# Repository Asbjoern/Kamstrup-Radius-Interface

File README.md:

# Kamstrup-Radius Interface
 ESP8266 interface for Kamstrup (Radius provided) electricity meter

Please also have a look the ESPHome component based on this code and working on the HAN module:\
https://github.com/Asbjoern/ESPHome-Kamstrup-Radius

This project interfaces with the Kampstrup electricity meter provided by Radius in Denmark.\
It decrypts the messages pushed on the HAN port and publishes the readings on MQTT.

There is also a proof of concept Python3 script (Kamstrup reader.py). Reads serialport connected to meter, decrypts, parses and publishes result to mqtt.  
Based on Python example provided by Radius.

## Project contains:
* HAN module for the Radius provided Kamstrup Omnipower electricity meters
* Arduino based software for a ESP8266 module. For receiving, decrypting and parsing push messages from meter.
* Publish data to MQTT

## Project uses: 
* Relevant files from mbed TLS library https://tls.mbed.org/
* Modified mbusparser library from Jalla2000's norwegian project https://github.com/jalla2000/kamstrup-mqtt
* Use Wifimanager library (or similar) to get captive portal and configuration

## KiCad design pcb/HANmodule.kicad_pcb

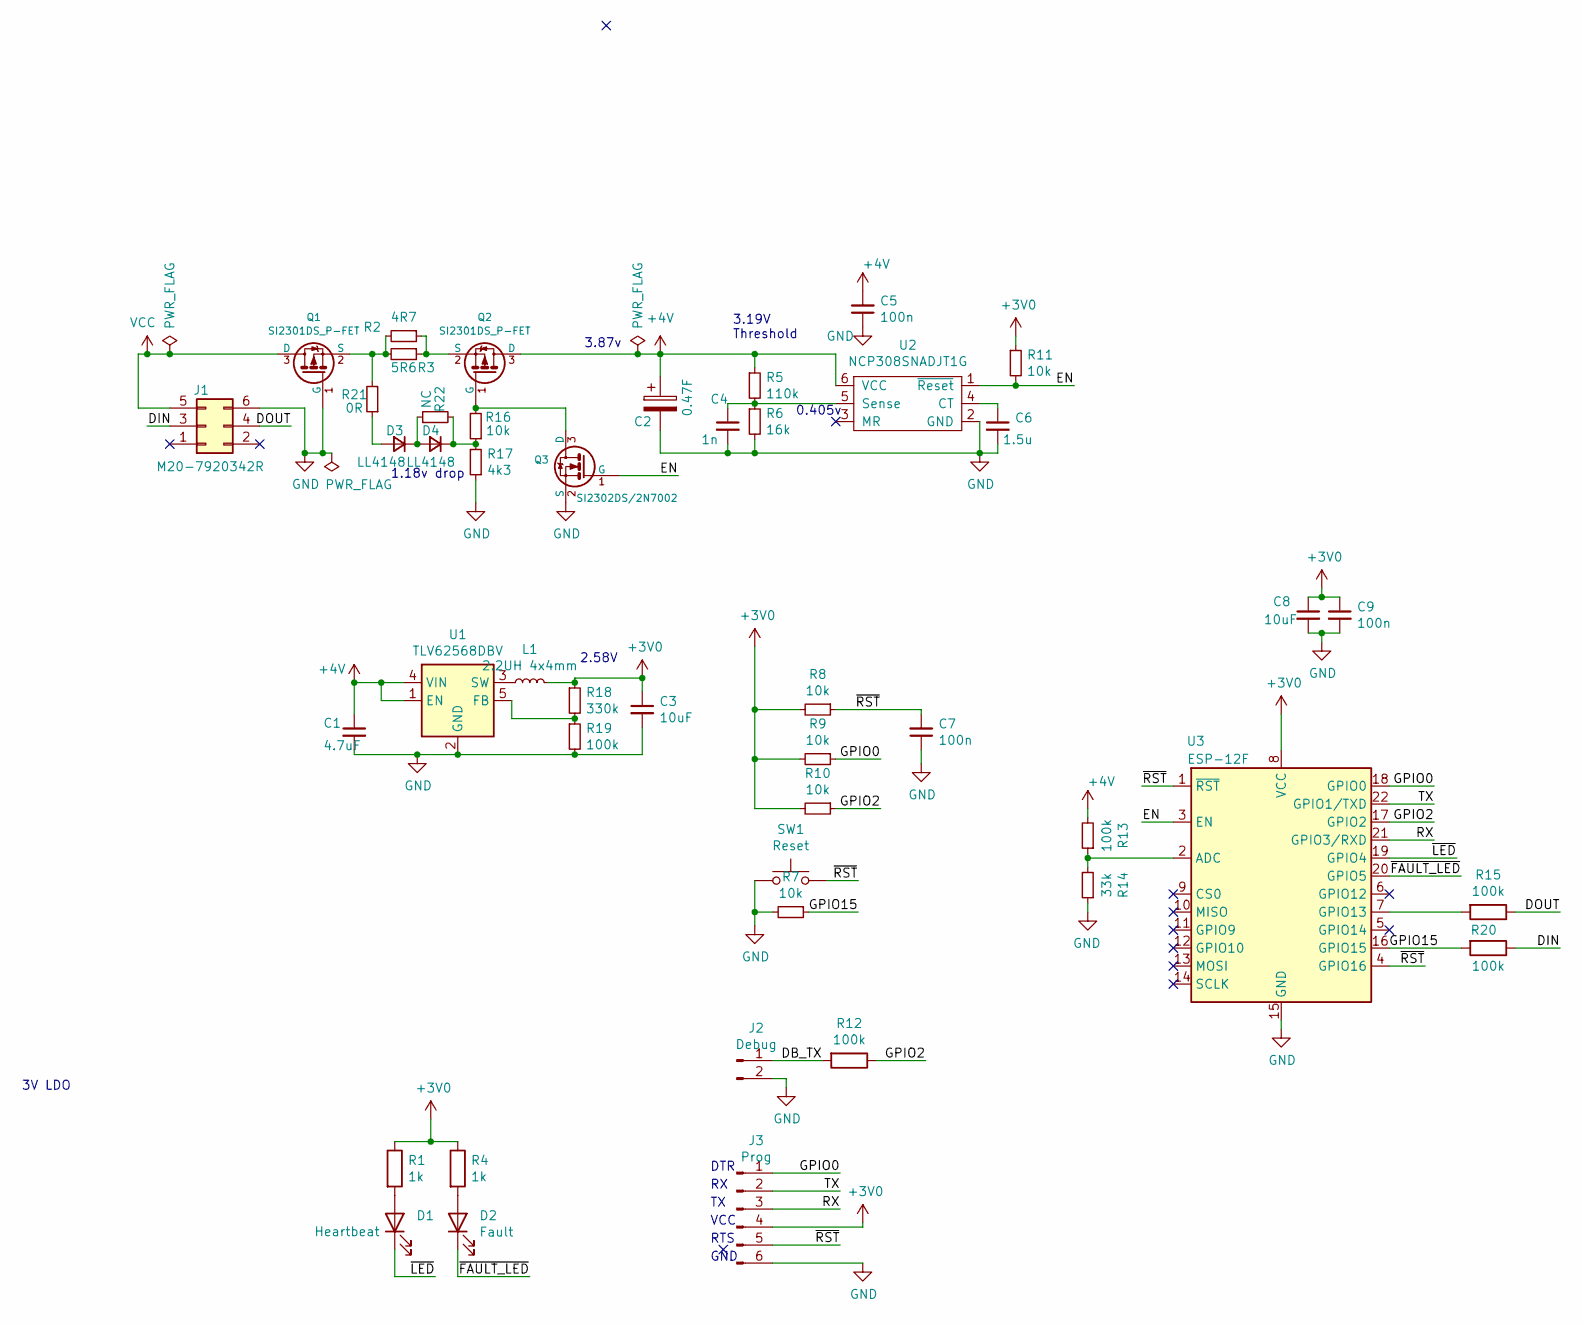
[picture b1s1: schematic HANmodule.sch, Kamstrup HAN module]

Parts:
C1: 4.7uF; C_0603_1608Metric
C2: 0.47F; c_sup 17,3x15x8.5P12
C3, C8: 10uF; C_0603_1608Metric_Pad1.05x0.95mm_HandSolder
C4: 1n; C_0603_1608Metric_Pad1.05x0.95mm_HandSolder
C5, C7, C9: 100n; C_0603_1608Metric_Pad1.05x0.95mm_HandSolder
C6: 1.5u; C_0603_1608Metric_Pad1.05x0.95mm_HandSolder
D1: Heartbeat; LED_0603_1608Metric
D2: Fault; LED_0603_1608Metric
D3, D4: LL4148; D_MiniMELF
J1: M20-7920342R
J2: Debug; PinHeader_1x02_P2.54mm_Horizontal
J3: Prog; PinHeader_1x06_P2.54mm_Horizontal
L1: 2.2UH 4x4mm; L_Bourns-SRN4018
Q1, Q2: SI2301DS_P-FET; SOT-23
Q3: SI2302DS/2N7002; SOT-23
R1, R4: 1k; R_0603_1608Metric_Pad1.05x0.95mm_HandSolder
R2: 4R7; R_0603_1608Metric_Pad1.05x0.95mm_HandSolder
R3: 5R6; R_0603_1608Metric_Pad1.05x0.95mm_HandSolder
R5: 110k; R_0603_1608Metric_Pad1.05x0.95mm_HandSolder
R6: 16k; R_0603_1608Metric_Pad1.05x0.95mm_HandSolder
R7, R8, R9, R10, R11, R16: 10k; R_0603_1608Metric_Pad1.05x0.95mm_HandSolder
R12, R13, R15, R19, R20: 100k; R_0603_1608Metric_Pad1.05x0.95mm_HandSolder
R14: 33k; R_0603_1608Metric_Pad1.05x0.95mm_HandSolder
R17: 4k3; R_0603_1608Metric_Pad1.05x0.95mm_HandSolder
R18: 330k; R_0603_1608Metric_Pad1.05x0.95mm_HandSolder
R21: 0R; R_0603_1608Metric_Pad1.05x0.95mm_HandSolder
R22: NC; R_0603_1608Metric_Pad1.05x0.95mm_HandSolder
SW1: Reset; Panasonic_EVQPUM_EVQPUD
U1: TLV62568DBV; SOT-23-5
U2: NCP308SNADJT1G; TSOP-6_1.65x3.05mm_P0.95mm
U3: ESP-12F; ESP-12E

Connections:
+3V0: C3.1, C8.1, C9.1, J3.4, L1.2, R1.1, R4.1, R8.2, R9.2, R10.2, R11.1, R18.1, U3.8 (VCC)
+4V: C1.1, C2.1, C5.2, Q2.3 (D), R5.1, R13.2, U1.1 (EN), U1.4 (VIN), U2.6 (VCC)
/DB_TX: J2.1, R12.2
/DIN: J1.3, R20.1
/DOUT: J1.4, R15.1
/EN: Q3.1 (G), R11.2, U2.1 (~Reset), U3.3 (EN)
/GPIO0: J3.1, R9.1, U3.18 (GPIO0)
/GPIO2: R10.1, R12.1, U3.17 (GPIO2)
/GPIO15: R7.1, R20.2, U3.16 (GPIO15)
/RX: J3.3, U3.21 (GPIO3/RXD)
/TX: J3.2, U3.22 (GPIO1/TXD)
/~FAULT_LED: D2.1 (K), U3.20 (GPIO5)
/~LED: D1.1 (K), U3.19 (GPIO4)
/~RST: C7.2, J3.5, R8.1, SW1.2, U3.1 (~RST), U3.4 (GPIO16)
GND: C1.2, C2.2, C3.2, C4.2, C5.1, C6.2, C7.1, C8.2, C9.2, J1.6, J2.2, J3.6, Q1.1 (G), Q3.2 (S), R6.2, R7.2, R14.1, R17.1, R19.2, SW1.1, U1.2 (GND), U2.2 (GND), U3.15 (GND)
unnamed: C4.1, R5.2, R6.1, U2.5 (Sense)
unnamed: C6.1, U2.4 (CT)
unnamed: D1.2 (A), R1.2
unnamed: D2.2 (A), R4.2
unnamed: D3.1 (K), D4.2 (A), R22.1
unnamed: D3.2 (A), R21.1
unnamed: D4.1 (K), R16.1, R17.2, R22.2
unnamed: L1.1, U1.3 (SW)
unnamed: Q1.2 (S), R2.2, R3.2, R21.2
unnamed: Q2.1 (G), Q3.3 (D), R16.2
unnamed: Q2.2 (S), R2.1, R3.1
unnamed: R13.1, R14.2, U3.2 (ADC)
unnamed: R15.2, U3.7 (GPIO13)
unnamed: R18.2, R19.1, U1.5 (FB)
VCC: J1.5, Q1.3 (D)

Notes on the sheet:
DTR
VCC
RTS
GND
3V LDO
0.405v
3.19V Threshold
2.58V
1.18v drop
3.87v

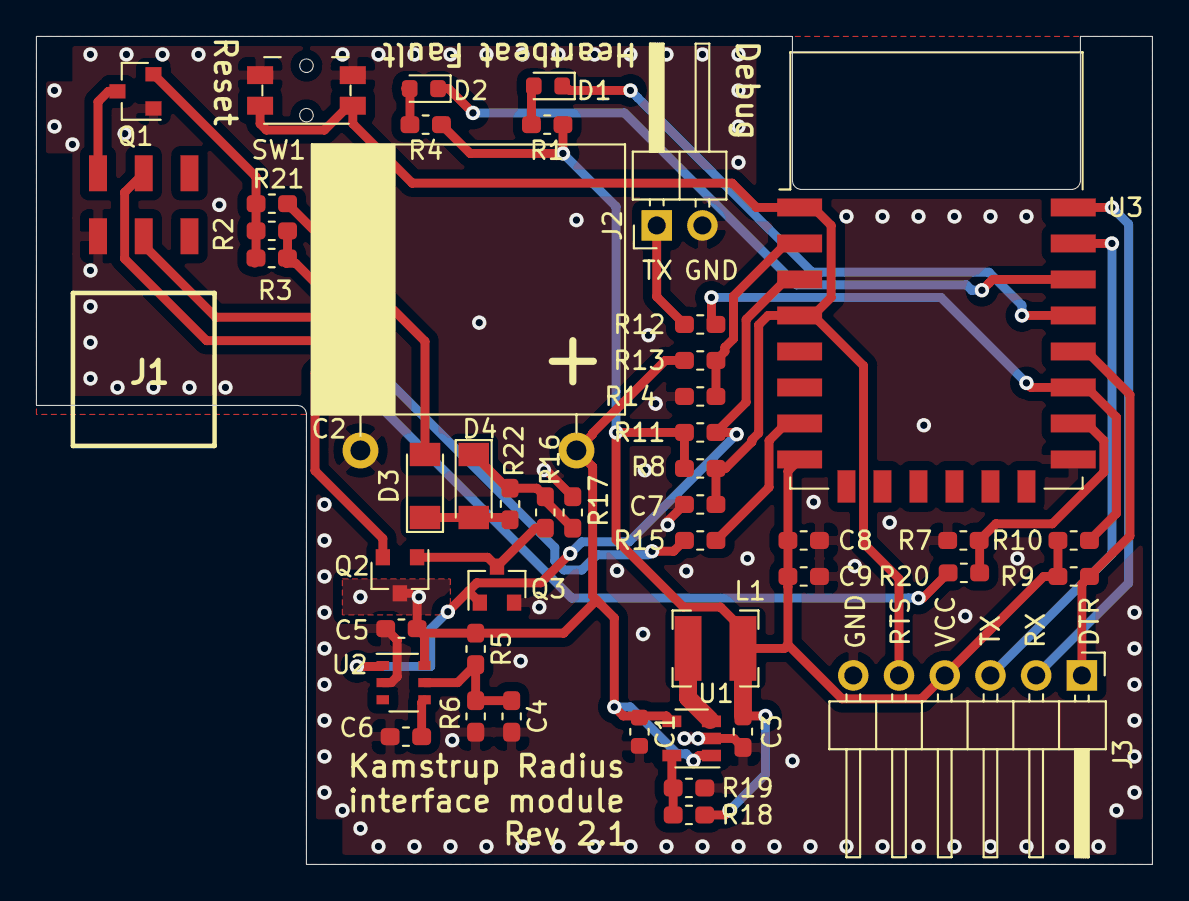
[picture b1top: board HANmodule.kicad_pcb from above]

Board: 2 copper layers, 62.0 x 46.0 mm, 46 parts (0 on the bottom side), 30 nets.

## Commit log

2020-01-22 Added documents
2020-01-22 Update Readne
2020-01-22 Proof of concept decryption added
    Based on Python example from Radius
2020-01-22 Update README.md
    Update readme
2020-01-22 fixed readme formatting
2020-01-22 mbusparserlibrary works on decrypted data
2020-01-23 Expanded mbusparser to include all packages from meter
2020-01-23 Uploaded proof of concept Python script
2020-01-23 Cleanup and added task list to readme
2020-01-23 Added initial PCB schematic and board layout
    Pending component selection and routing
2024-05-17 PCB rev 1
2024-05-17 Working on meter
2024-05-17 Added MQTT topic to configuration and mDNS
2024-05-17 fix readme formatting
2024-05-17 Added initial wifimanager configuration.
    Not happy about current configuration not loaded to config page
2024-05-17 Updated schematic
2024-05-17 Switched to persWifimanager and added configuration
2024-05-17 Redirect debug serial
2024-05-17 Upload case drawing
2024-05-17 Added MQTT. Needs more testing
2024-05-17 Nu pullup on RX and LED function
2024-05-17 PCB rev2 to be tested
2024-05-17 Revert "Fix key array size to allow place for string termination charactor"
    This reverts commit d4a1c2259eabe1475e3634fdb90036012d61e9cc.
2024-05-17 Fix mqtt login with username/password
2024-05-17 Fix key array size to allow place for string termination charactor
2024-05-17 Improved power design
2024-05-17 Only connect to mqtt if not in APmode and better username/password handling
2024-05-17 fix mDNS
2024-05-17 Update readme to reflect project i working and complete
